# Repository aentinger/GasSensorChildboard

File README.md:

💾 Gas Sensor Childboard
========================

# 📸 Image

# 📂 Description

The LXRobotics Gas Sensor Childboard can be used to sense various gas types e.g. LPG, butane, propane, methane, alcohol, hydrogen, smoke. The sensitivity of the sensor can be adjusted via potentiometer. A user controllable red LED and a piezo buzzer are used for signalling alarm/warning states. For a quick and easy start, an open source Arduino library with sample programs is available.

**Features**

* MQ-2 gas sensor (LPG, butane, propane, methane, alcohol, hydrogen, smoke)
* Power supply of the gas sensor can be turned off in order to save energy
* Adjustable sensitivity of the gas sensor via potentiometer
* Piezo-buzzer for alarm tones
* Red signal LED
* Can be used with the Radioshield and the Childboard Adaptershield
* Arduino Library with example programs is available on GitHub

# 🎥 [Video](images/gas_sensor_childboard_demo.mp4)

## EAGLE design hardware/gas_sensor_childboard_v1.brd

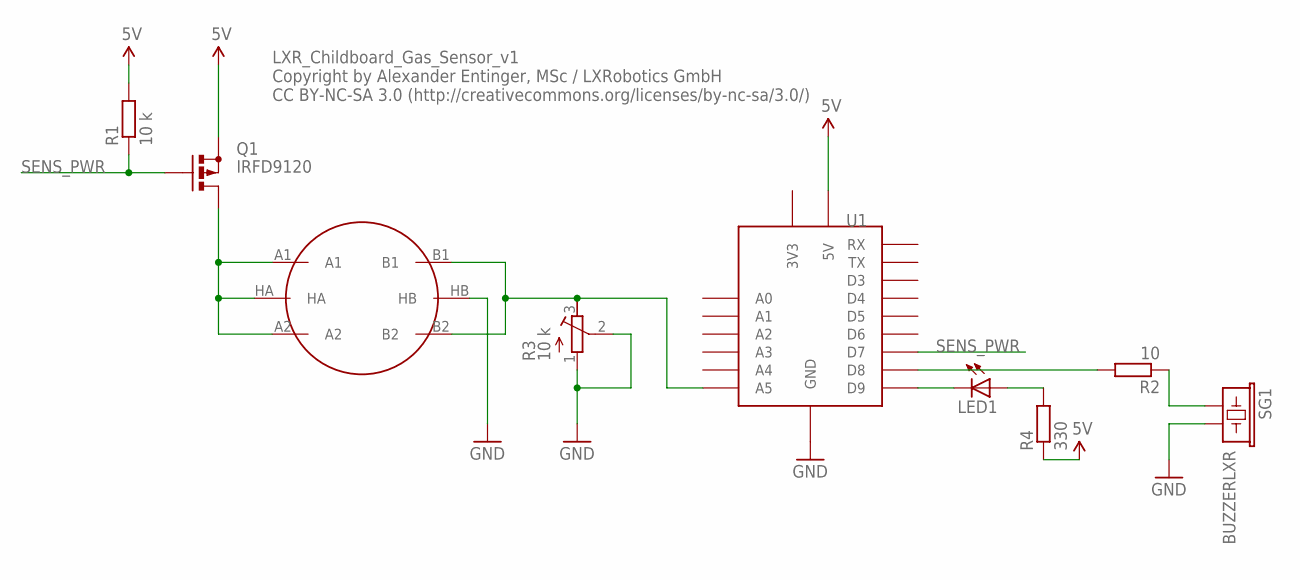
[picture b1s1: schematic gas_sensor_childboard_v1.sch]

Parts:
LED1: 5 mm RED; LED5MM
MQ-2: METHANE_SENSOR; MQ-3
Q1: IRFD9120; C370-01
R1: 10 k; 0207/7
R2: 10; 0207/7
R3: 10 k; RTRIM3339P
R4: 330; 0207/7
SG1: BUZZERLXR; BUZZER_LXR
U1: RF_CHILDBOARD_CONRF_C; RF_CHILDBOARD_CON

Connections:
5V: Q1.S, R1.2, R4.1, U1.5V
GND: MQ-2.HB, R3.1 (E), R3.2 (S), SG1.2, U1.GND, U1.GND1 (GND), U1.GND2 (GND)
unnamed: MQ-2.A1, MQ-2.A2, MQ-2.HA, Q1.D, Q1.D1 (D)
unnamed: MQ-2.B1, MQ-2.B2, R3.3 (A), U1.A5
unnamed: R2.1, SG1.1
unnamed: R2.2, U1.D8
unnamed: LED1.A, R4.2
unnamed: LED1.K (C), U1.D9
SENS_PWR: Q1.G, R1.1, U1.D7

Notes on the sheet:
LXR_Childboard_Gas_Sensor_v1 Copyright by Alexander Entinger, MSc / LXRobotics GmbH CC BY-NC-SA 3.0 (http://creativecommons.org/licenses/by-nc-sa/3.0/)

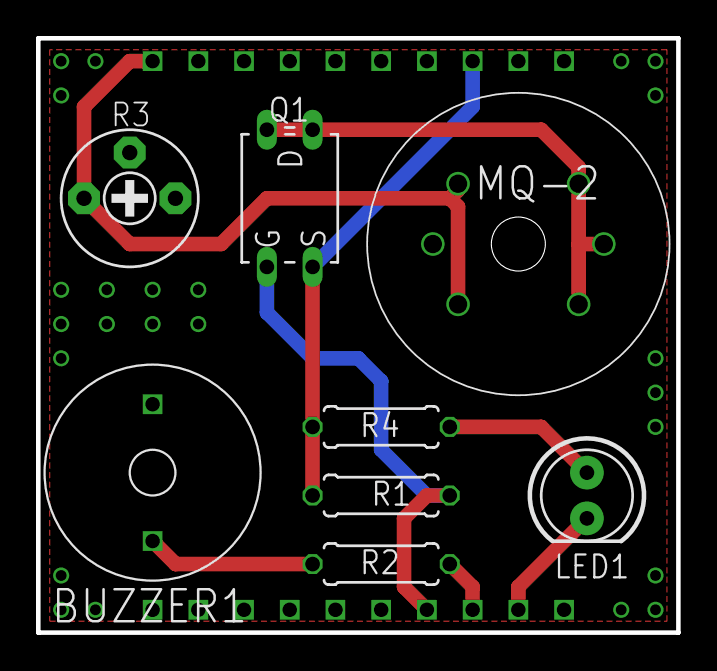
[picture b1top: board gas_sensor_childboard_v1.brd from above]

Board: 2 copper layers, 35.6 x 33.0 mm, 9 parts (0 on the bottom side), 9 nets.

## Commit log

2014-01-09 initial checkin of files for lxr childboard gas sensor
2014-01-15 initial checkin of software for gassensor
2017-06-27 Adding hardware + images
2025-03-26 Upload BOM.
2025-03-26 Add demo video.
2025-03-26 Pretty up README.

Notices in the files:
README.md:
License: CC BY-NC-SA 4.0
parts and their libraries:
SparkFun-Sensors: Licensing: CC v3.0 Share-Alike You are welcome to use this library for commercial purposes.
